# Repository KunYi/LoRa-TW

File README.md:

# LoRa-TW

**LoRa-TW** is a hardware project designed in **KiCAD** targeting LoRa applications in the Taiwan frequency band(AS923, 920MHz ~ 925MHz).
The design is based on the **Semtech SX1262** transceiver, optimized for robust operation in noisy RF environments.

## Project Purpose
This project aims to provide a reliable LoRa module reference design for Taiwan (center frequency **922.5 MHz**).
To improve receiver robustness, an external **SAW filter** is introduced in the RX path to mitigate interference from nearby cellular communication bands.

## Key Features
- **RF Core**: Semtech SX1262
- **T/R Switch**: PSemi RF switch
- **Filtering**: QUALCOMM SAW filter (optimized for 922.5 MHz center frequency)
- **Powering**: DC-DC mode operation
- **Form Factor**: 12-pin 2.0mm breakout for easy integration

## Pinout
| Pin | Name   | Description                   |
|-----|--------|-------------------------------|
| 1   | VDD    | Power supply                  |
| 2   | CS     | Chip Select                   |
| 3   | VDD    | Power supply                  |
| 4   | SCLK   | SPI Clock                     |
| 5   | GND    | Ground                        |
| 6   | MOSI   | SPI Data (Master Out)         |
| 7   | GND    | Ground                        |
| 8   | MISO   | SPI Data (Master In)          |
| 9   | DIO1   | Interrupt / IRQ               |
| 10  | /RESET | Reset                         |
| 11  | RXEN   | RX Enable (T/R Switch)        |
| 12  | BUSY   | SX1262 Busy status            |

## Repository Contents
- `LoRa-TW.kicad_pcb` - KiCAD project
- `LoRa-TW.kicad_sch` – KiCAD schematic files
- `LoRa-TW.kicad_pcb` – KiCAD PCB layout files

## Author
**KUN-YI CHEN**,
📧 [kunyi.chen@gmail.com](mailto:kunyi.chen@gmail.com)

- **Current Version:** v1 (250823) – First release of the hardware design.
- **Status:** Schematic and PCB completed, awaiting validation and testing.
- **Planned Improvements:**
  - Conduct full RF testing and verification in Taiwan ISM band.
  - Optimize layout for improved RF isolation and matching.

## License
This project is licensed under the **CERN Open Hardware License v2 - Strongly Reciprocal (CERN-OHL-S-2.0)**.
You are free to use, modify, and distribute this design, but derivative works must also be shared under the same license.

For details, see the [LICENSE](LICENSE) file.

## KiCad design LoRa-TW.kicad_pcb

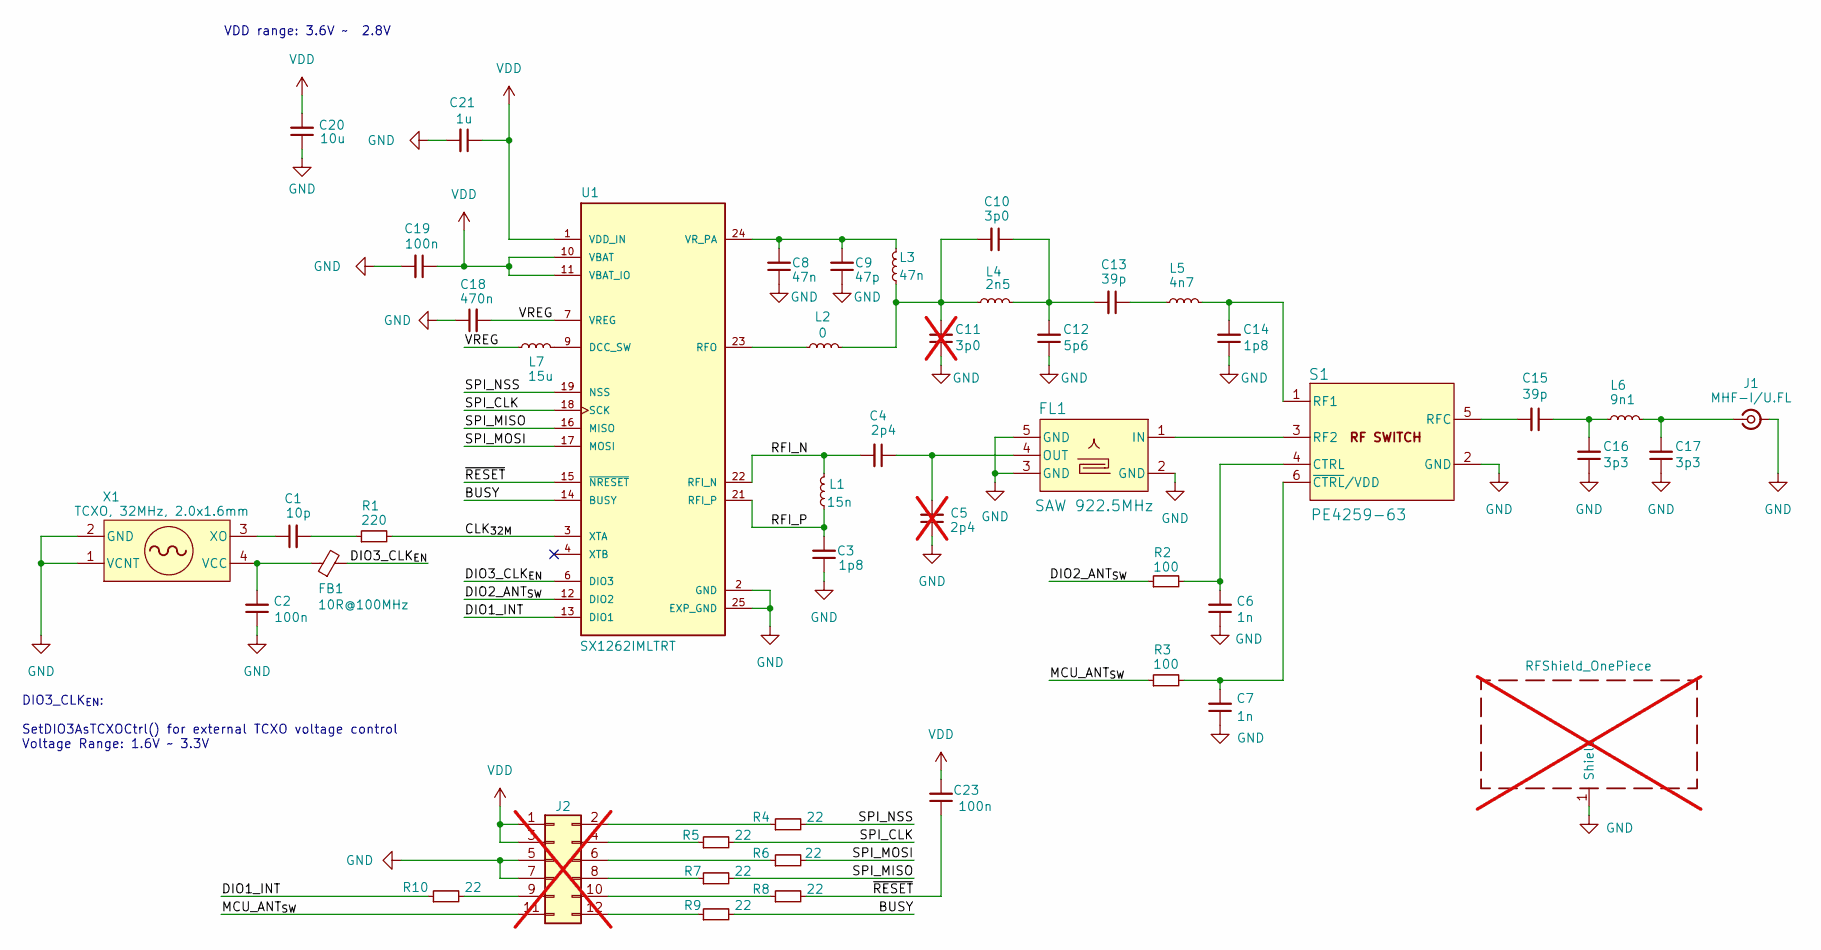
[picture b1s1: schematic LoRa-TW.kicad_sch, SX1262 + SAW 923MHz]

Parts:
C1: 10p; C_HF_0402_1005Metric; Part No GJM1555C1H100JB01D
C2, C19, C23: 100n; C_HF_0402_1005Metric; Part No GRM155R71H104KE14D
C3, C14: 1p8; C_HF_0402_1005Metric; Part No GJM1555C1H1R8BB01D
C4: 2p4; C_HF_0402_1005Metric; Part No GJM1555C1H2R4BB01D
C5: 2p4; C_HF_0402_1005Metric; Part No GJM1555C1H2R4BB01D; not fitted
C6, C7: 1n; C_HF_0402_1005Metric; Part No GRM155R72A102KA01D
C8: 47n; C_HF_0402_1005Metric; Part No GRM155R71C473KA01D
C9: 47p; C_HF_0402_1005Metric; Part No GJM1555C1H470JB01D
C10: 3p0; C_HF_0402_1005Metric; Part No GJM1555C1H3R0BB01D
C11: 3p0; C_HF_0402_1005Metric; Part No GJM1555C1H3R0BB01D; not fitted
C12: 5p6; C_HF_0402_1005Metric; Part No GJM1555C1H5R6CB01D
C13, C15: 39p; C_HF_0402_1005Metric; Part No GJM1555C1H390JB01D
C16, C17: 3p3; C_HF_0402_1005Metric; Part No GJM1555C1H3R3BB01D
C18: 470n; C_HF_0402_1005Metric; Part No GRM155R71A474KE01D
C20: 10u; C_0805_2012Metric; Part No GRM21BR71A106KA3L
C21: 1u; C_0603_1608Metric; Part No 0603B105K250CT
FB1: 10R@100MHz; R_HF_0402_1005Metric; Part No BLM15PG100SN1D
FL1: SAW 922.5MHz; SAW_1411; Part No TA2710AA1322
J1: MHF-I/U.FL; IPEX_20279-001E-03; Part No 20279-001E-03
J2: Conn_02x06_2.0mm; PinHeader_2x06_P2.00mm_Vertical; not fitted
J3: RFShield_OnePiece; ShieldCan; not fitted
L1: 15n; L_HF_0402_1005Metric; Part No LQW15AN15NH00D
L2: 0; L_HF_0402_1005Metric; Part No CRCW04020000Z0EDC
L3: 47n; L_HF_0402_1005Metric; Part No LQW15AN47NJ00D
L4: 2n5; L_HF_0402_1005Metric; Part No LQW15AN2N5C00D
L5: 4n7; L_HF_0402_1005Metric; Part No LQW15AN4N7C00D
L6: 9n1; L_HF_0402_1005Metric; Part No LQW15AN9N1H00D
L7: 15u; L_0805_2012Metric; Part No MLZ2012M150WT000
R1: 220; R_HF_0402_1005Metric; Part No CRCW0402220RJNED
R2, R3: 100; R_HF_0402_1005Metric; Part No CRCW0402100RJNED
R4, R5, R6, R7, R8, R9, R10: 22; R_HF_0402_1005Metric; Part No CRCW040222R0JNED
S1: PE4259-63; SC-70-6_PSM; Part No PE4259-63
U1: SX1262IMLTRT; PARTREV 1.1
X1: TCXO, 32MHz, 2.0x1.6mm; NT2016SA_NDK; Part No NT2016SA-32MHz-END4263A/NT2016SF-END426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

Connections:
/BUSY: R9.2, U1.14 (BUSY)
/CLK_{32M}: R1.2, U1.3 (XTA)
/DIO1_INT: R10.1, U1.13 (DIO1)
/DIO2_ANT_{SW}: R2.1, U1.12 (DIO2)
/DIO3_CLK_{EN}: FB1.2, U1.6 (DIO3)
/MCU_ANT_{SW}: J2.11, R3.1
/RFI_N: C4.2, L1.2, U1.22 (RFI_N)
/RFI_P: C3.2, L1.1, U1.21 (RFI_P)
/SPI_CLK: R5.2, U1.18 (SCK)
/SPI_MISO: R7.2, U1.16 (MISO)
/SPI_MOSI: R6.2, U1.17 (MOSI)
/SPI_NSS: R4.2, U1.19 (NSS)
/VREG: C18.2, L7.1, U1.7 (VREG)
/~RESET: C23.1, R8.2, U1.15 (~NRESET)
GND: C2.1, C3.1, C5.1, C6.1, C7.1, C8.1, C9.1, C11.1, C12.1, C14.1, C16.1, C17.1, C18.1, C19.2, C20.1, C21.2, FL1.2 (GND), FL1.3 (GND), FL1.5 (GND), J1.2, J1.3, J2.5, J2.7, J3.1 (Shield), S1.2 (GND), U1.2 (GND), U1.5 (GND), U1.8 (GND), U1.20 (GND), U1.25 (EXP_GND), X1.1 (VCNT), X1.2 (GND)
unnamed: C1.2, R1.1
unnamed: C10.1, C12.2, C13.2, L4.2
unnamed: C10.2, C11.2, L2.2, L3.1, L4.1
unnamed: C13.1, L5.1
unnamed: C15.1, C16.2, L6.1
unnamed: C17.2, J1.1, L6.2
unnamed: FL1.1 (IN), S1.3 (RF2)
unnamed: C4.1, C5.2, FL1.4 (OUT)
unnamed: J2.2, R4.1
unnamed: J2.4, R5.1
unnamed: J2.6, R6.1
unnamed: J2.8, R7.1
unnamed: J2.9, R10.2
unnamed: J2.10, R8.1
unnamed: J2.12, R9.1
unnamed: C6.2, R2.2, S1.4 (CTRL)
unnamed: C14.2, L5.2, S1.1 (RF1)
unnamed: C15.2, S1.5 (RFC)
unnamed: C7.2, R3.2, S1.6 (~CTRL/VDD)
unnamed: L7.2, U1.9 (DCC_SW)
unnamed: L2.1, U1.23 (RFO)
unnamed: C8.2, C9.2, L3.2, U1.24 (VR_PA)
unnamed: C2.2, FB1.1, X1.4 (VCC)
unnamed: C1.1, X1.3 (XO)
VDD: C19.1, C20.2, C21.1, C23.2, J2.1, J2.3, U1.1 (VDD_IN), U1.10 (VBAT), U1.11 (VBAT_IO)

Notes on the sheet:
DIO3_CLK_{EN}: SetDIO3AsTCXOCtrl() for external TCXO voltage control Voltage Range: 1.6V ~ 3.3V
VDD range: 3.6V ~ 2.8V

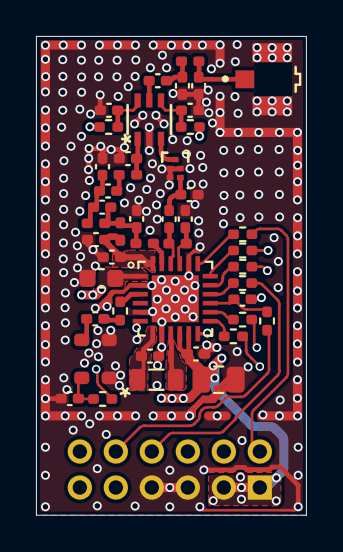
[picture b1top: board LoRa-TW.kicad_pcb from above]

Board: 4 copper layers, 15.0 x 26.6 mm, 47 parts (1 on the bottom side), 40 nets.

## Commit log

2025-08-15 import basice components symbol/footprint
2025-08-15 Add some datasheet and step file
    - Update NT2016SA Step file
    - Add 32MHz TCXO NT2016SA/TG-5006CJ datasheet
2025-08-17 update receive of schematic
    - update symbol
    - place rx path components
2025-08-17 update transmit of schematic
    - update TX path
    - correct some components properties
2025-08-18 add IPEX/U.FL 3D Model
    - add I-PEX MHF-I Datasheet
    - add U.FL and MHF-I 3D Model
2025-08-18 add I-PEX MHF-I RF connector sym/fp
2025-08-18 update schematic for power input
2025-08-18 add project owner 0402 footprint for reduce area
2025-08-18 update schematic & pcb for new footprint
2025-08-19 add JLC PCB stack
2025-08-19 Add SAW Filter 3D model by FreeCAD
2025-08-19 add new JLC PCB stack with PP-7628
2025-08-20 update SAW Filter properties with 3D Model
2025-08-20 update layout for RF parts
2025-08-21 add shielding can
2025-08-21 update layout part
2025-08-22 fine turning layout
2025-08-22 update RXEN/TXEN information in schematic
2025-08-22 update layout of pcb
2025-08-22 remove unnecessary files
2025-08-22 add TDK shield inductor 15uH datasheet
2025-08-22 update 15uH for sch and pcb
2025-08-22 remove unused stackup info
2025-08-23 prepare for BOM generation
2025-08-23 add README.md and LICENSE
2025-08-23 add new SAW filter for ISM 915MHz for reference
2025-08-23 update footprints
2025-08-23 update footprint of PCB for DRC check and fine turning
2025-08-24 update description of components
2025-08-24 sych. properties of schematic to pcb
2025-08-24 adjustion gen. column of BOM options
2025-08-25 optimization DC2DC layout
2025-08-25 optimization layout
2025-08-26 update footprints and 3D Models
    - rename or update some properties
    - update shielding metal can
2025-08-26 update SAW filter to use TST TA2710AA1322
2025-08-26 update and fine turning
2025-08-28 PCB release version
    Add LCSC part number into footprint properties
2025-08-28 change datasheet of SAW filter location
2025-08-28 update SAW Filter 3030 symbol & update 3D model
2025-08-28 add relase for JLC PCB/SMT
2025-08-29 add 0R_Jump sym & footprint
